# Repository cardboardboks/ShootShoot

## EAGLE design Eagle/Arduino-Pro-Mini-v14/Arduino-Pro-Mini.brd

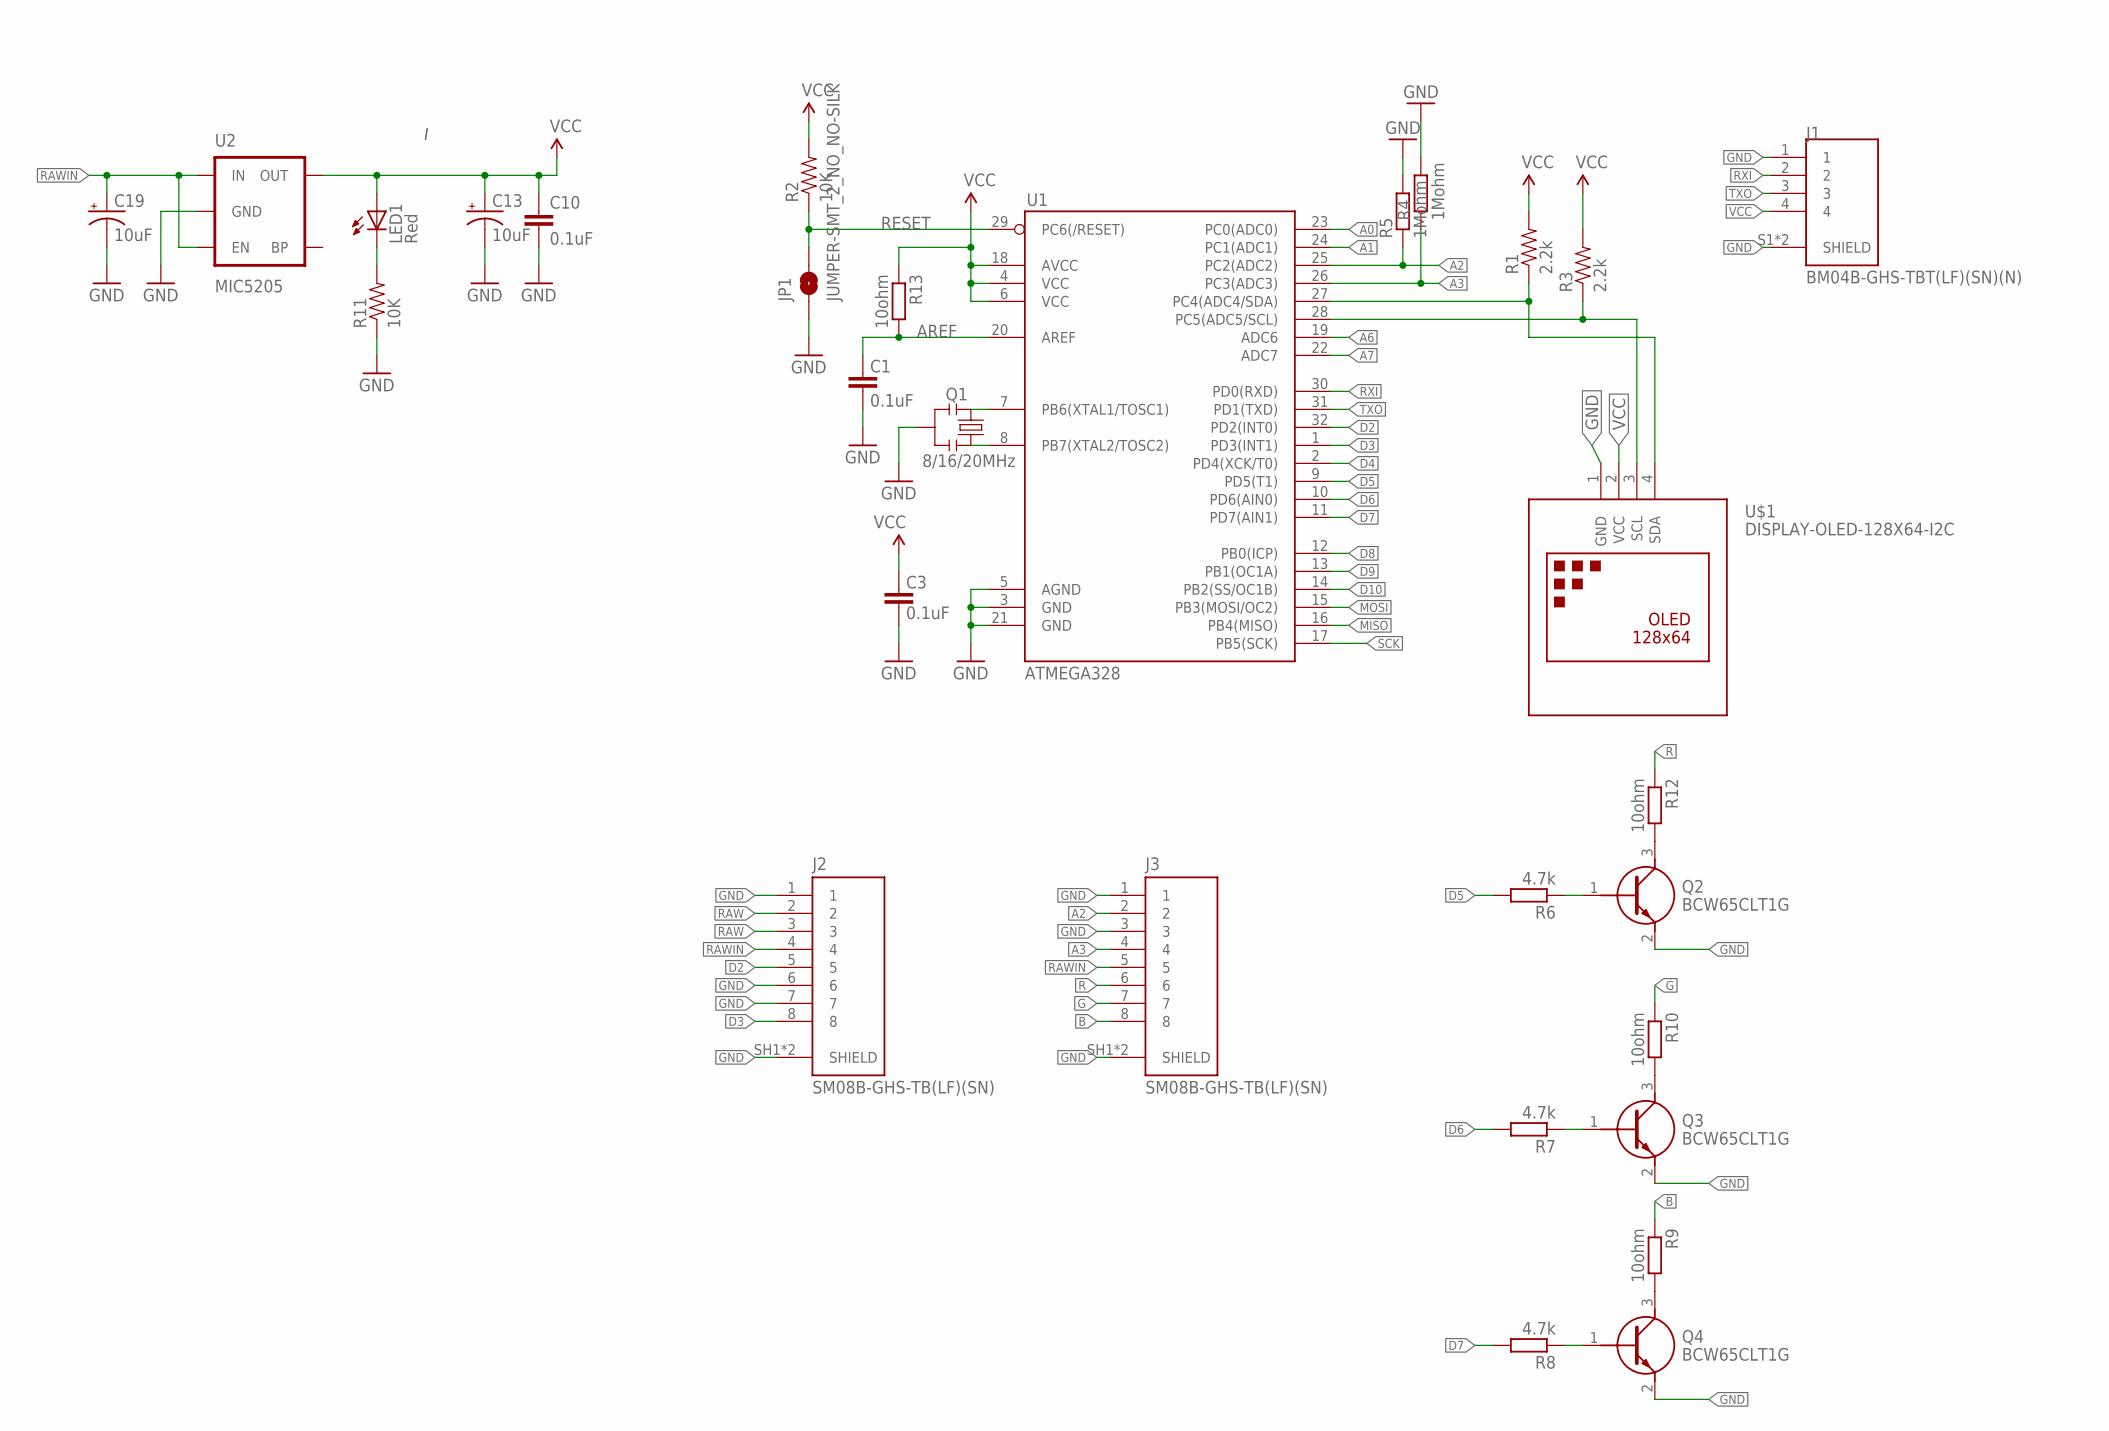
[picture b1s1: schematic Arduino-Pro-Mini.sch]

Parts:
C1, C3, C10: 0.1uF; 0603-CAP
C13, C19: 10uF; EIA3216
J1: BM04B-GHS-TBT(LF)(SN)(N); JST_BM04B-GHS-TBT(LF)(SN)(N)
J2, J3: SM08B-GHS-TB(LF)(SN); JST_SM08B-GHS-TB(LF)(SN)
JP1: JUMPER-SMT_2_NO_NO-SILK; SMT-JUMPER_2_NO_NO-SILK
LED1: Red; 0603-LED-ALT1
Q1: 8/16/20MHz; RESONATOR-SMD-1:1
Q2, Q3, Q4: BCW65CLT1G; SOT96P237X111-3N
R1, R3: 2.2k; 0603-RES
R2, R11: 10K; 0603-RES
R4, R5: 1Mohm; R0402
R6, R7, R8: 4.7k; R0402
R9, R10, R12, R13: 10ohm; R0402
U1: ATMEGA328; TQFP32-08
U2: MIC5205; SOT23-5
U$1: DISPLAY-OLED-128X64-I2C

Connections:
A0: U1.23 (PC0(ADC0))
A1: U1.24 (PC1(ADC1))
A2: J3.2, R5.1, U1.25 (PC2(ADC2))
A3: J3.4, R4.1, U1.26 (PC3(ADC3))
A4: R1.1, U1.27 (PC4(ADC4/SDA)), U$1.4 (SDA)
A5: R3.1, U1.28 (PC5(ADC5/SCL)), U$1.3 (SCL)
A6: U1.19 (ADC6)
A7: U1.22 (ADC7)
AREF: C1.2, R13.2, U1.20 (AREF)
B: J3.8, R9.1
D2: J2.5, U1.32 (PD2(INT0))
D3: J2.8, U1.1 (PD3(INT1))
D4: U1.2 (PD4(XCK/T0))
D5: R6.2, U1.9 (PD5(T1))
D6: R7.2, U1.10 (PD6(AIN0))
D7: R8.2, U1.11 (PD7(AIN1))
D8: U1.12 (PB0(ICP))
D9: U1.13 (PB1(OC1A))
D10: U1.14 (PB2(SS/OC1B))
G: J3.7, R10.1
GND: C1.1, C3.1, C10.2, C13.C (-), C19.C (-), J1.1, J1.S1 (SHIELD), J1.S2 (SHIELD), J2.1, J2.6, J2.7, J2.SH1 (SHIELD), J2.SH2 (SHIELD), J3.1, J3.3, J3.SH1 (SHIELD), J3.SH2 (SHIELD), JP1.1, Q1.2, Q2.2 (E), Q3.2 (E), Q4.2 (E), R4.2, R5.2, R11.1, U1.3 (GND), U1.5 (AGND), U1.21 (GND), U2.2 (GND), U$1.1 (GND)
MISO: U1.16 (PB4(MISO))
MOSI: U1.15 (PB3(MOSI/OC2))
unnamed: Q1.3, U1.8 (PB7(XTAL2/TOSC2))
unnamed: Q1.1, U1.7 (PB6(XTAL1/TOSC1))
unnamed: Q4.1 (B), R8.1
unnamed: LED1.C, R11.2
unnamed: Q3.1 (B), R7.1
unnamed: Q2.1 (B), R6.1
unnamed: Q4.3 (C), R9.2
unnamed: Q3.3 (C), R10.2
unnamed: Q2.3 (C), R12.2
R: J3.6, R12.1
RAW: J2.2, J2.3
RAWIN: C19.A (+), J2.4, J3.5, U2.1 (IN), U2.3 (EN)
RESET: JP1.2, R2.1, U1.29 (PC6(/RESET))
RXI: J1.2, U1.30 (PD0(RXD))
SCK: U1.17 (PB5(SCK))
TXO: J1.3, U1.31 (PD1(TXD))
VCC: C3.2, C10.1, C13.A (+), J1.4, LED1.A, R1.2, R2.2, R3.2, R13.1, U1.4 (VCC), U1.6 (VCC), U1.18 (AVCC), U2.5 (OUT), U$1.2 (VCC)

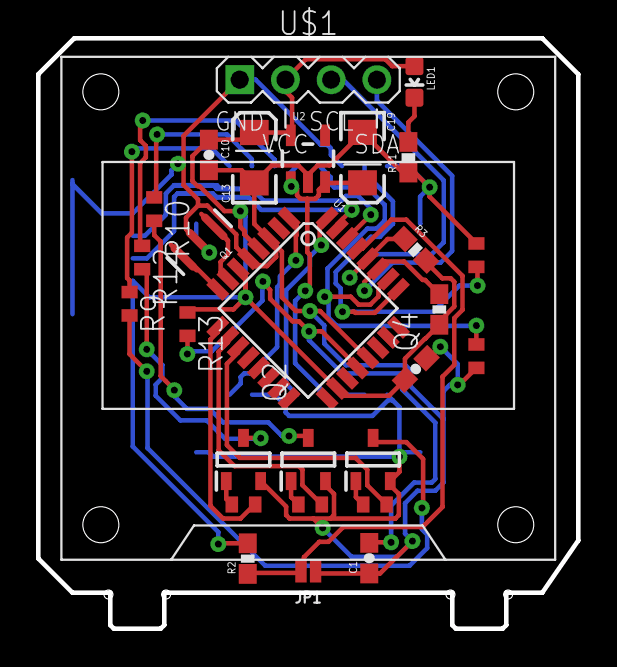
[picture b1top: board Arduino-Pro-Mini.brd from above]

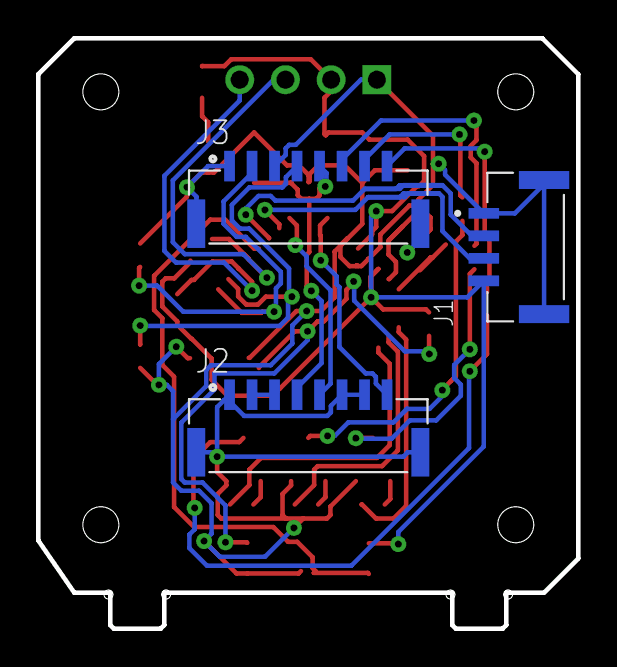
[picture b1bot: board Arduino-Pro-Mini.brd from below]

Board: 2 copper layers, 30.0 x 32.8 mm, 30 parts (3 on the bottom side), 29 nets.

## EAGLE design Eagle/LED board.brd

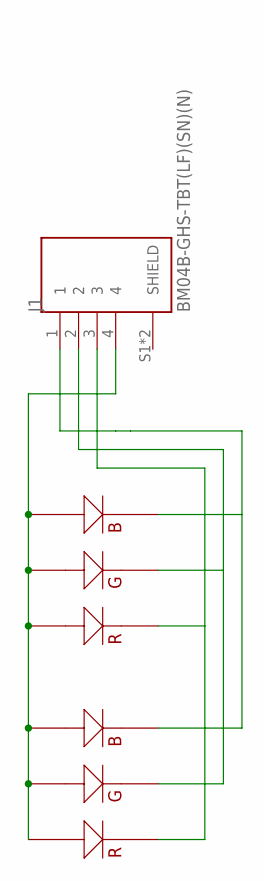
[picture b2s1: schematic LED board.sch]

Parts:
J1: BM04B-GHS-TBT(LF)(SN)(N); JST_BM04B-GHS-TBT(LF)(SN)(N)
U$1, U$2: 3WRGB

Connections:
unnamed: J1.3, U$1.R-, U$2.R-
unnamed: J1.2, U$1.G-, U$2.G-
unnamed: J1.1, U$1.B-, U$2.B-
unnamed: J1.4, U$1.B+, U$1.G+, U$1.R+, U$2.B+, U$2.G+, U$2.R+

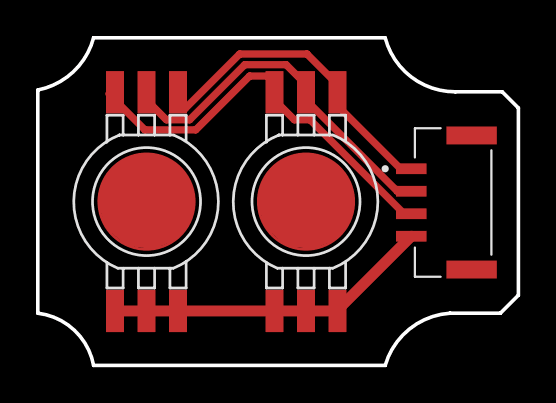
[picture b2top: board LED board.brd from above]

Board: 2 copper layers, 26.7 x 18.2 mm, 3 parts (0 on the bottom side), 4 nets.

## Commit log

2019-11-10 Setup
2019-11-10 Added LED driers
2019-11-19 LED board
2019-11-25 things
2019-12-03 Auto stash before merge of "master" and "origin/master"
2019-12-03 fix merge issue

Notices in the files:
parts and their libraries:
SparkFun-Jumpers: Licensing: Creative Commons ShareAlike 4.0 International - https://creativecommons.org/licenses/by-sa/4.0
diy-modules: Released under the Creative Commons Attribution 4.0 International License: http://creativecommons.org/licenses/by/4.0
